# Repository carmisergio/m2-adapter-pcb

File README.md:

# m2-adapter-pcb
A simple PCB which allows a SATA M.2 SSD to be connected to a regular SATA cable.

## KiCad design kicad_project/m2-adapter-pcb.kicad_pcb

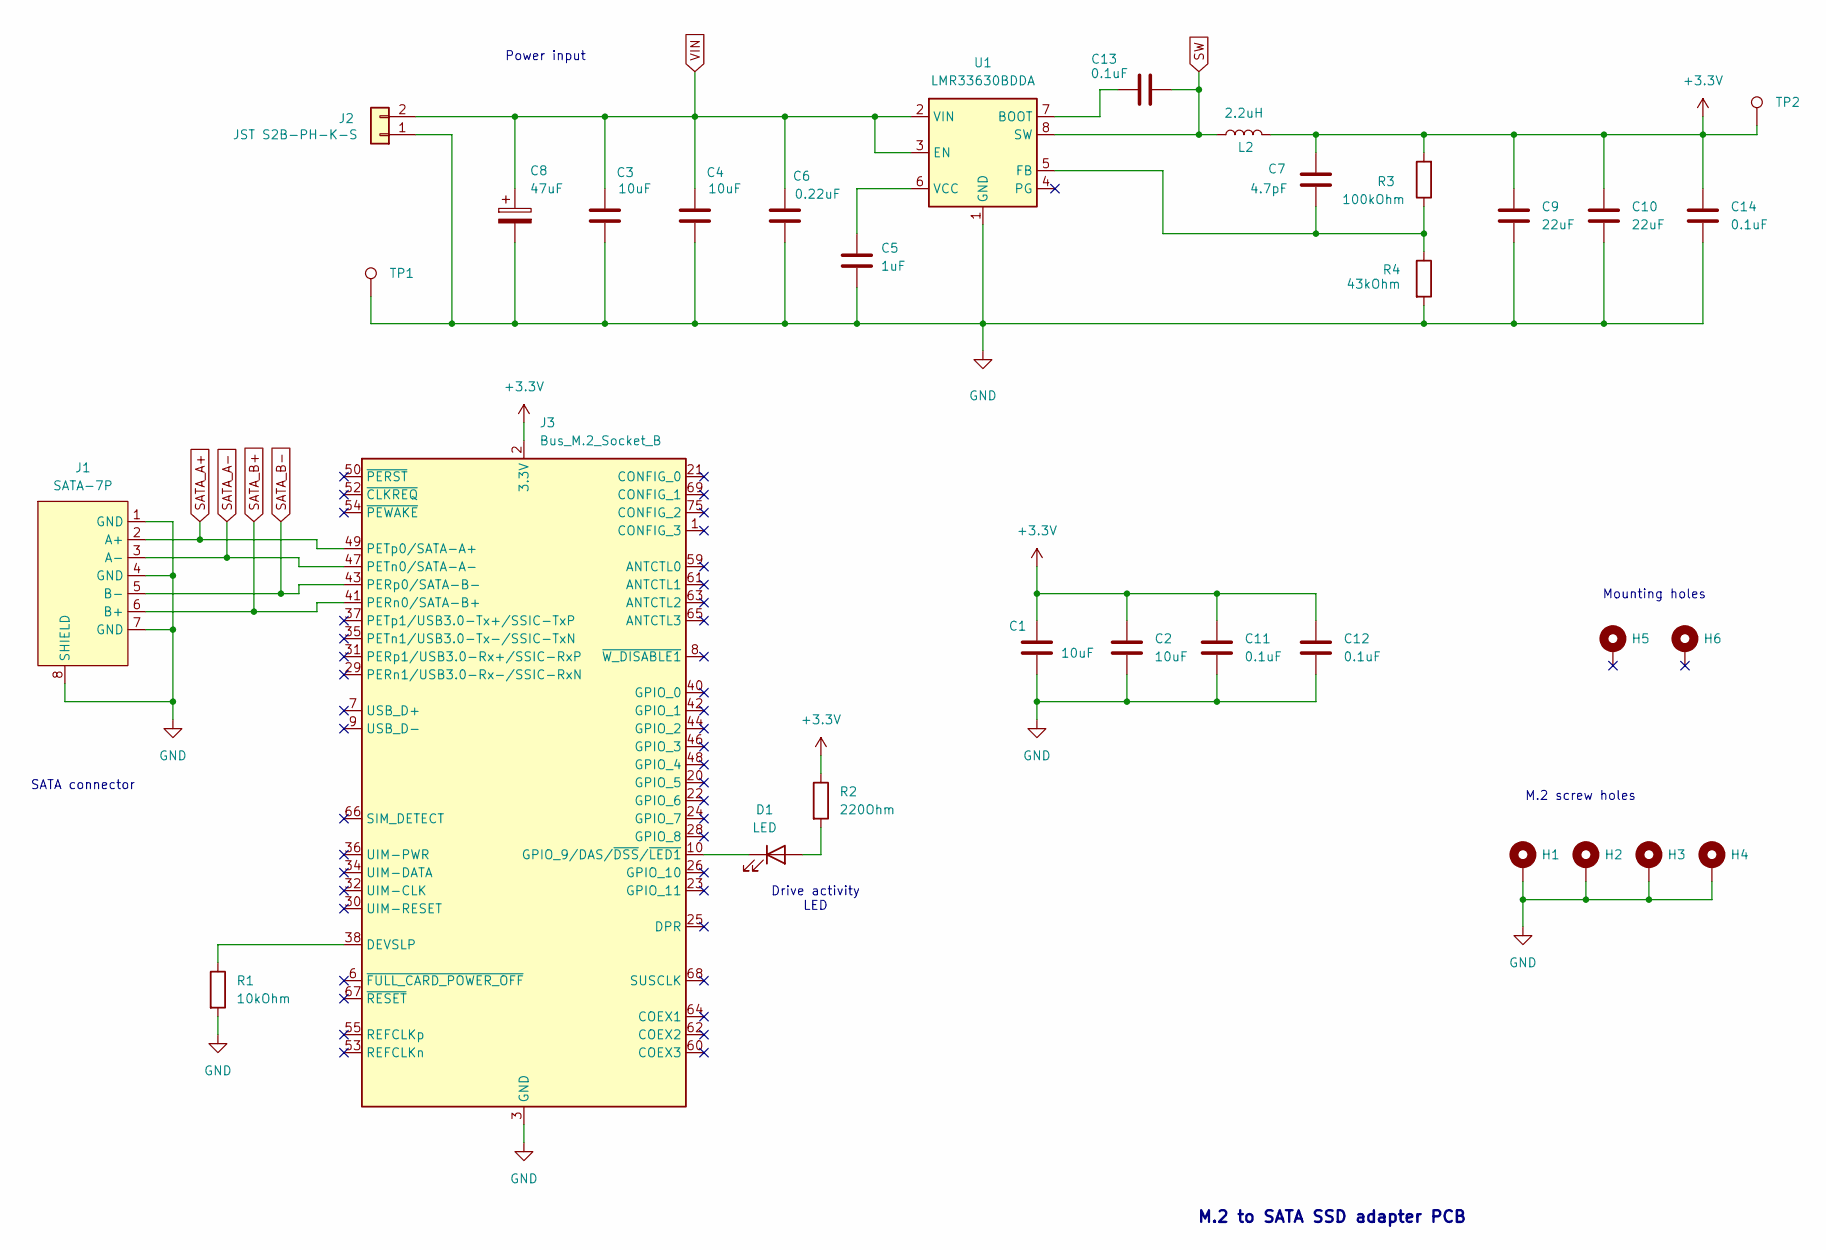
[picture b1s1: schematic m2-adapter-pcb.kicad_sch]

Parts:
C1, C2, C3, C4: 10uF; C_1206_3216Metric_Pad1.33x1.80mm_HandSolder
C5: 1uF; C_0805_2012Metric_Pad1.18x1.45mm_HandSolder
C6: 0.22uF; C_0805_2012Metric_Pad1.18x1.45mm_HandSolder
C7: 4.7pF; C_0603_1608Metric_Pad1.08x0.95mm_HandSolder
C8: 47uF; C_Elec_6.3x5.8
C9, C10: 22uF; C_1210_3225Metric_Pad1.33x2.70mm_HandSolder
C11, C12, C13, C14: 0.1uF; C_0603_1608Metric_Pad1.08x0.95mm_HandSolder
D1: LED; LED_0805_2012Metric_Pad1.15x1.40mm_HandSolder
H1, H2, H3, H4: MountingHole_Pad; M.2_Standoff_Hole
H5, H6: MountingHole_Pad; MountingHole_2.2mm_M2_Pad
J1: SATA-7P; AMPHENOL_SAT3M2132072TR
J2: JST S2B-PH-K-S; JST_PH_S2B-PH-K_1x02_P2.00mm_Horizontal
J3: Bus_M.2_Socket_B; AMPHENOL_MDT420B03001
L2: 2.2uH; L_AMDLA4530S
R1: 10kOhm; C_0603_1608Metric_Pad1.08x0.95mm_HandSolder
R2: 220Ohm; C_0603_1608Metric_Pad1.08x0.95mm_HandSolder
R3: 100kOhm; C_0603_1608Metric_Pad1.08x0.95mm_HandSolder
R4: 43kOhm; C_0603_1608Metric_Pad1.08x0.95mm_HandSolder
TP1, TP2: TestPoint; TestPoint_Pad_D2.0mm
U1: LMR33630BDDA; Texas_HSOP-8-1EP_3.9x4.9mm_P1.27mm_ThermalVias_HandSolder

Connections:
+3.3V: C1.1, C2.1, C7.1, C9.1, C10.1, C11.1, C12.1, C14.1, J3.2 (3.3V), J3.4 (3.3V), J3.70 (3.3V), J3.72 (3.3V), J3.74 (3.3V), L2.2, R2.1, R3.2, TP2.1
GND: C1.2, C2.2, C3.2, C4.2, C5.2, C6.2, C8.2, C9.2, C10.2, C11.2, C12.2, C14.2, H1.1, H2.1, H3.1, H4.1, J1.1 (GND), J1.4 (GND), J1.7 (GND), J1.8 (SHIELD), J2.1, J3.3 (GND), J3.5 (GND), J3.11 (GND), J3.27 (GND), J3.33 (GND), J3.39 (GND), J3.45 (GND), J3.51 (GND), J3.57 (GND), J3.71 (GND), J3.73 (GND), J3.P1 (GND), J3.P2 (GND), R1.2, R4.2, TP1.1, U1.1 (GND), U1.9 (GND)
unnamed: D1.2 (A), R2.2
unnamed: D1.1 (K), J3.10 (GPIO_9/DAS/~DSS/~LED1)
unnamed: J3.38 (DEVSLP), R1.1
unnamed: C13.1, U1.7 (BOOT)
unnamed: C7.2, R3.1, R4.1, U1.5 (FB)
unnamed: C5.1, U1.6 (VCC)
SATA_A+: J1.2 (A+), J3.49 (PETp0/SATA-A+)
SATA_A-: J1.3 (A-), J3.47 (PETn0/SATA-A-)
SATA_B+: J1.6 (B+), J3.41 (PERn0/SATA-B+)
SATA_B-: J1.5 (B-), J3.43 (PERp0/SATA-B-)
SW: C13.2, L2.1, U1.8 (SW)
VIN: C3.1, C4.1, C6.1, C8.1, J2.2, U1.2 (VIN), U1.3 (EN)

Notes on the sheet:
Drive activity LED
SATA connector
M.2 screw holes
M.2 to SATA SSD adapter PCB
Power input
Mounting holes

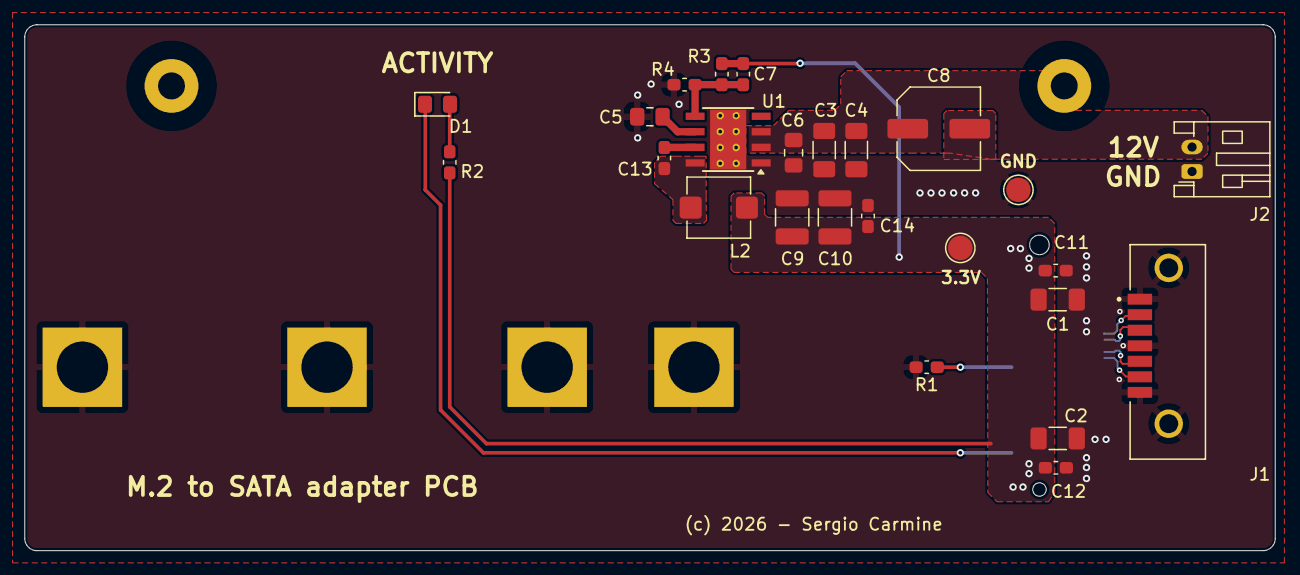
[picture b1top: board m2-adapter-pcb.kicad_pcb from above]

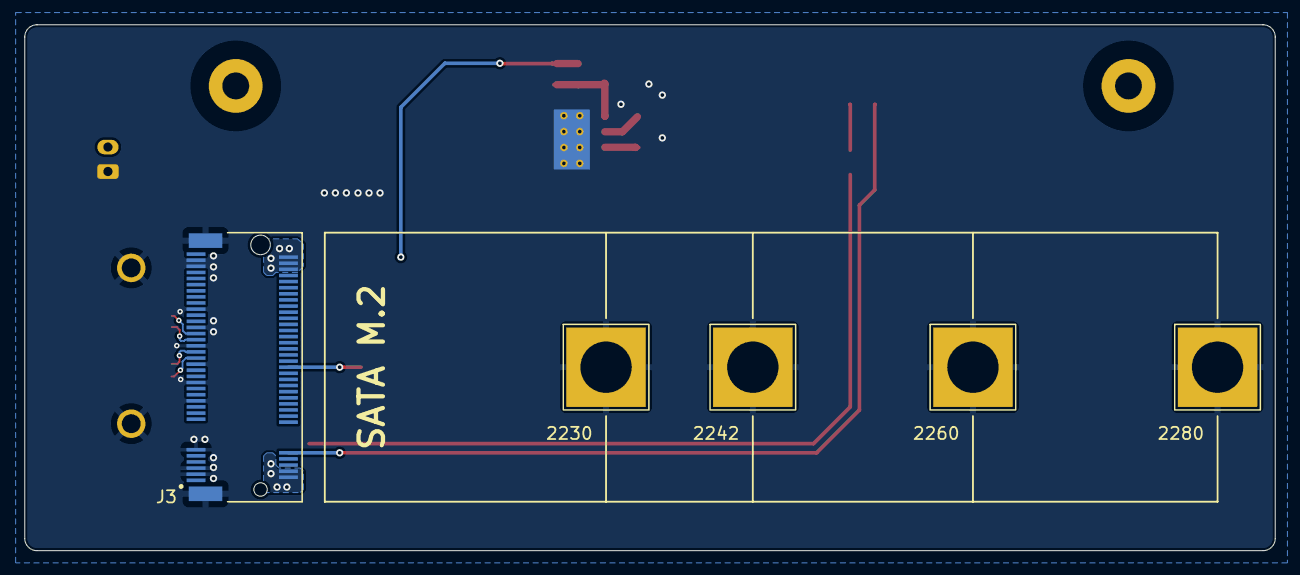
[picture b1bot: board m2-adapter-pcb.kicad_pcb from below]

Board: 2 copper layers, 102.2 x 43.0 mm, 32 parts (5 on the bottom side), 14 nets.

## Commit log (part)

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2026-01-28 Project setup
2026-01-31 Finish schematics
2026-02-03 Update buck converter schematics
2026-02-03 Finish routing
2026-02-04 Implement easy suggestions
2026-02-08 Buck converter redesign
2026-02-09 Final design
2026-02-13 Add test points
2026-02-15 Final production design

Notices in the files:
kicad_project/m2-adapter-pcb.kicad_pcb:
(c) 2026 - Sergio Carmine
